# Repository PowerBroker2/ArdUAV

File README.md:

<br />

Code repository for ground station and flight control software for experimental Arduino UAVs (fixed wing).

# First Flight with ArdUAV:

# Current Test Bird:

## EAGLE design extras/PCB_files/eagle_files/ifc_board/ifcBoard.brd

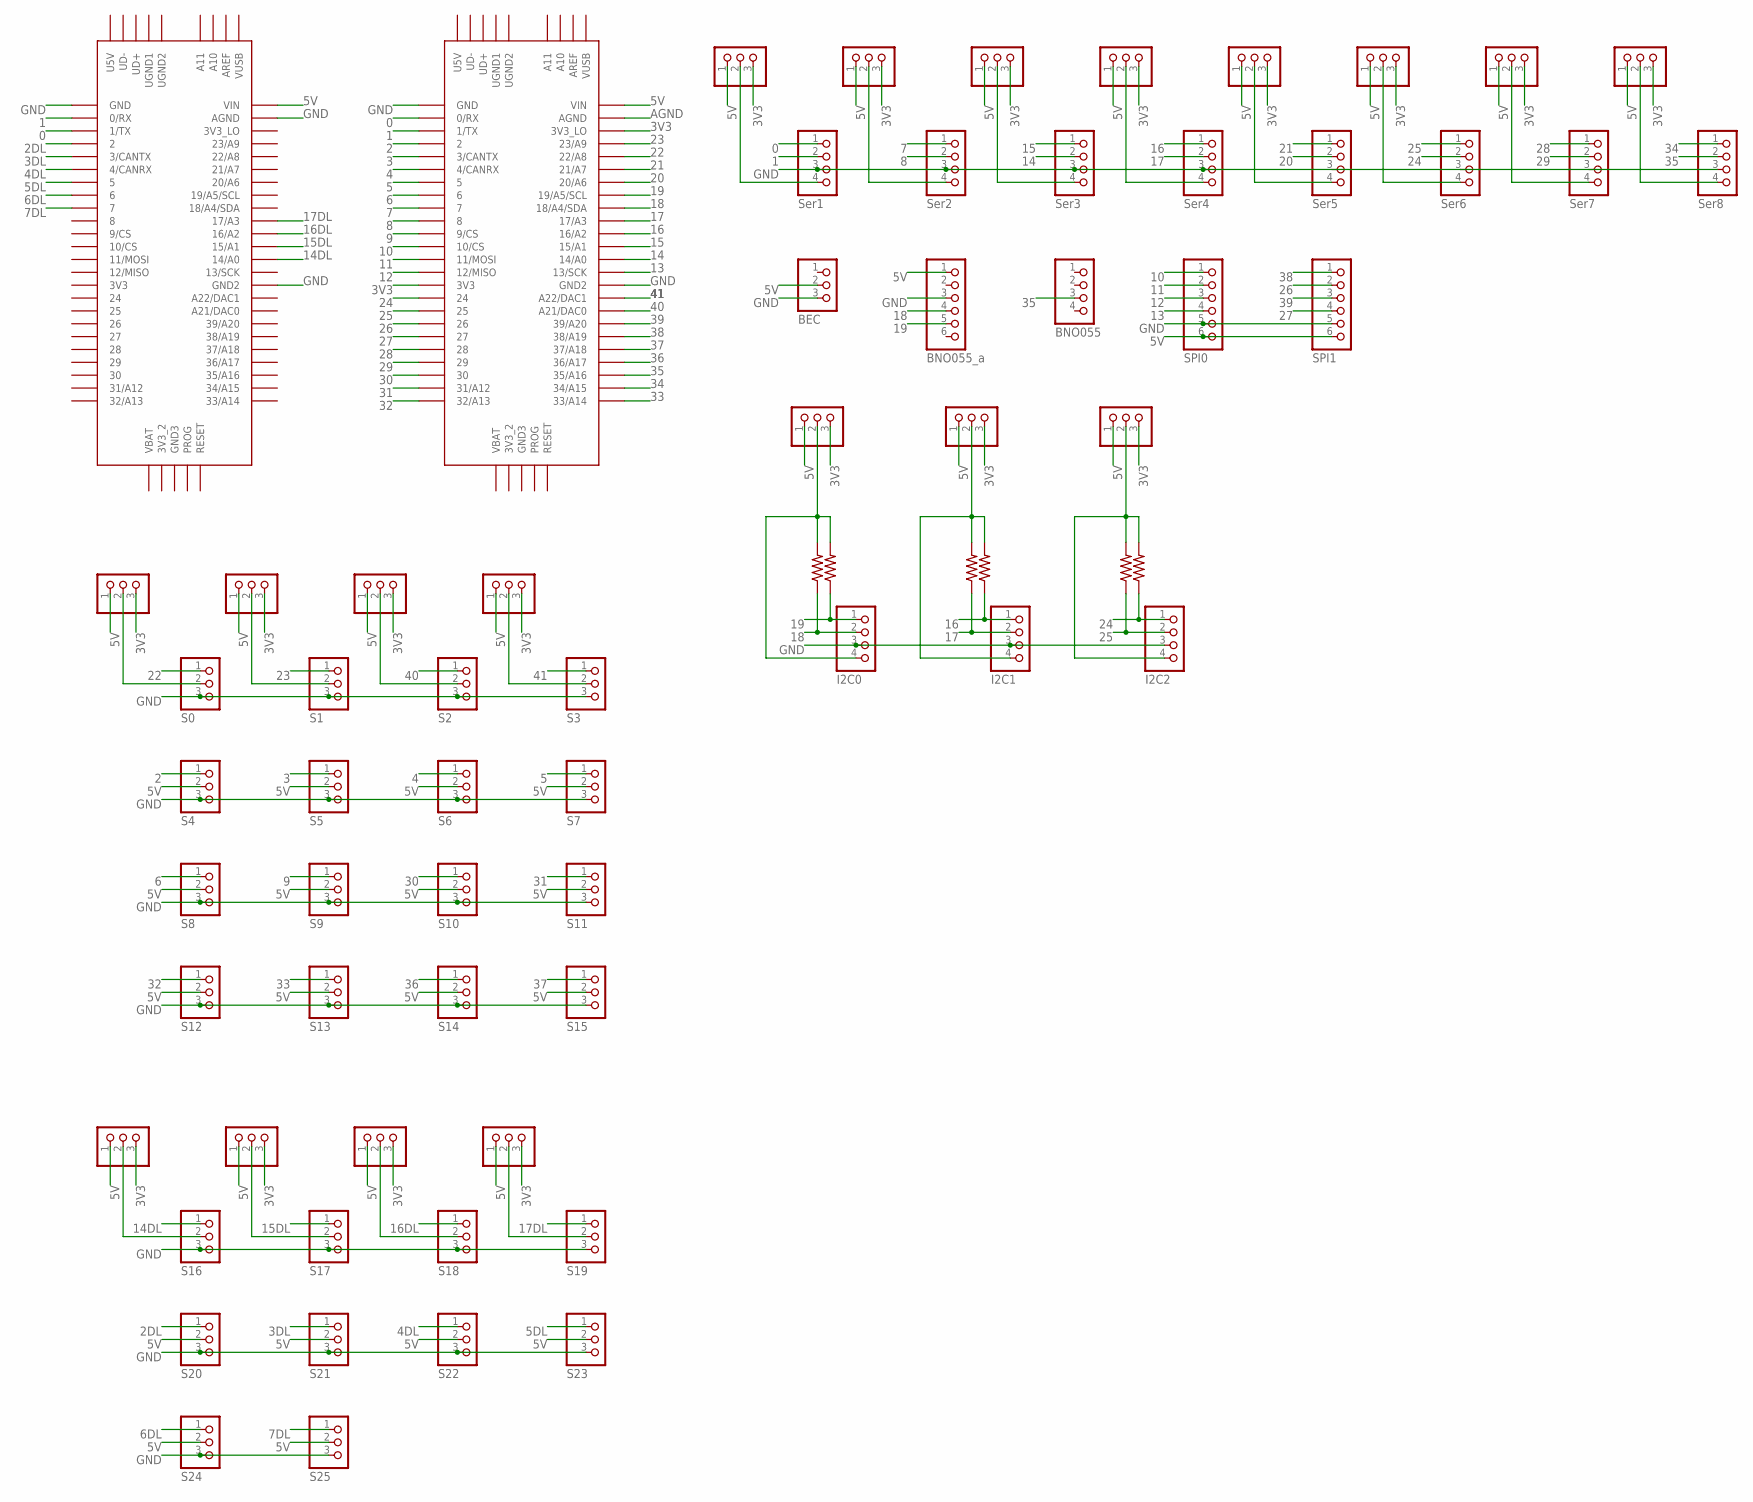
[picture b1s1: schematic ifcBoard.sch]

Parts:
JP1: BEC; 1X03
JP2, JP19, JP20, JP35, JP36, JP37, JP38, JP39, JP40, JP41, JP42, JP43, JP44, JP45, JP46, JP47, JP64, JP65, JP66, JP67: S0; 1X03
JP3: S1; 1X03
JP4: S2; 1X03
JP5: S3; 1X03
JP6: S4; 1X03
JP7: S5; 1X03
JP8: S6; 1X03
JP9: S7; 1X03
JP10: S8; 1X03
JP11: S9; 1X03
JP12: S10; 1X03
JP13: S11; 1X03
JP14: S12; 1X03
JP15: S13; 1X03
JP16: S14; 1X03
JP17: S15; 1X03
JP18: Ser6; 1X04
JP21: Ser7; 1X04
JP22: I2C0; 1X04
JP23: Ser1; 1X04
JP24: Ser2; 1X04
JP25: Ser3; 1X04
JP26: Ser4; 1X04
JP27: Ser5; 1X04
JP28: I2C1; 1X04
JP29: I2C2; 1X04
JP30: Ser8; 1X04
JP31: SPI0; 1X06
JP32: SPI1; 1X06
JP33: BNO055_a; 1X06
JP34: BNO055; 1X04
JP58: S16; 1X03
JP59: S17; 1X03
JP60: S18; 1X03
JP61: S19; 1X03
JP62: S23; 1X03
JP63: S22; 1X03
JP68: S21; 1X03
JP69: S20; 1X03
JP70: S24; 1X03
JP71: S25; 1X03
R2, R3, R4, R5, R6, R7: R-US_0207/12; 0207/12
U$1, U$2: TEENSY_3.5/3.6

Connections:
0: JP23.1, U$1.0/RX, U$2.1/TX
1: JP23.2, U$1.1/TX, U$2.0/RX
2: JP6.1, U$1.2
2DL: JP69.1, U$2.2
3: JP7.1, U$1.3/CANTX
3DL: JP68.1, U$2.3/CANTX
3V3: JP19.3, JP20.3, JP35.3, JP36.3, JP37.3, JP38.3, JP39.3, JP40.3, JP41.3, JP42.3, JP43.3, JP44.3, JP45.3, JP46.3, JP47.3, JP64.3, JP65.3, JP66.3, JP67.3, U$1.3V3, U$1.3V3_LO
4: JP8.1, U$1.4/CANRX
4DL: JP63.1, U$2.4/CANRX
5: JP9.1, U$1.5
5DL: JP62.1, U$2.5
5V: JP1.2, JP6.2, JP7.2, JP8.2, JP9.2, JP10.2, JP11.2, JP12.2, JP13.2, JP14.2, JP15.2, JP16.2, JP17.2, JP19.1, JP20.1, JP22.4, JP31.6, JP32.6, JP33.1, JP35.1, JP36.1, JP37.1, JP38.1, JP39.1, JP40.1, JP40.2, JP41.1, JP42.1, JP43.1, JP44.1, JP45.1, JP46.1, JP47.1, JP62.2, JP63.2, JP64.1, JP65.1, JP66.1, JP67.1, JP68.2, JP69.2, JP70.2, JP71.2, R2.2, R3.2, U$1.VIN, U$2.VIN
6: JP10.1, U$1.6
6DL: JP70.1, U$2.6
7: JP24.1, U$1.7
7DL: JP71.1, U$2.7
8: JP24.2, U$1.8
9: JP11.1, U$1.9/CS
10: JP31.1, U$1.10/CS
11: JP31.2, U$1.11/MOSI
12: JP31.3, U$1.12/MISO
13: JP31.4, U$1.13/SCK
14: JP25.2, U$1.14/A0
14DL: JP58.1, U$2.14/A0
15: JP25.1, U$1.15/A1
15DL: JP59.1, U$2.15/A1
16: JP26.1, JP28.1, R6.1, U$1.16/A2
16DL: JP60.1, U$2.16/A2
17: JP26.2, JP28.2, R4.1, U$1.17/A3
17DL: JP61.1, U$2.17/A3
18: JP22.2, JP33.4, R2.1, U$1.18/A4/SDA
19: JP22.1, JP33.5, R3.1, U$1.19/A5/SCL
20: JP27.2, U$1.20/A6
21: JP27.1, U$1.21/A7
22: JP2.1, U$1.22/A8
23: JP3.1, U$1.23/A9
24: JP18.2, JP29.1, R5.1, U$1.24
25: JP18.1, JP29.2, R7.1, U$1.25
26: JP32.2, U$1.26
27: JP32.4, U$1.27
28: JP21.1, U$1.28
29: JP21.2, U$1.29
30: JP12.1, U$1.30
31: JP13.1, U$1.31/A12
32: JP14.1, U$1.32/A13
33: JP15.1, U$1.33/A14
34: JP30.1, U$1.34/A15
35: JP30.2, JP34.3, U$1.35/A16
36: JP16.1, U$1.36/A17
37: JP17.1, U$1.37/A18
38: JP32.1, U$1.38/A19
39: JP32.3, U$1.39/A20
40: JP4.1, U$1.21/DAC0 (A21/DAC0)
41: JP5.1, U$1.A22/DAC1
AGND: U$1.AGND
GND: JP1.3, JP2.3, JP3.3, JP4.3, JP5.3, JP6.3, JP7.3, JP8.3, JP9.3, JP10.3, JP11.3, JP12.3, JP13.3, JP14.3, JP15.3, JP16.3, JP17.3, JP18.3, JP21.3, JP22.3, JP23.3, JP24.3, JP25.3, JP26.3, JP27.3, JP28.3, JP29.3, JP30.3, JP31.5, JP32.5, JP33.3, JP58.3, JP59.3, JP60.3, JP61.3, JP62.3, JP63.3, JP68.3, JP69.3, JP70.3, JP71.3, U$1.GND, U$1.GND2, U$2.AGND, U$2.GND, U$2.GND2
unnamed: JP19.2, JP23.4
unnamed: JP58.2, JP64.2
unnamed: JP59.2, JP65.2
unnamed: JP60.2, JP66.2
unnamed: JP61.2, JP67.2
unnamed: JP20.2, JP24.4
unnamed: JP25.4, JP35.2
unnamed: JP26.4, JP36.2
unnamed: JP2.2, JP42.2
unnamed: JP27.4, JP37.2
unnamed: JP29.4, JP44.2, R5.2, R7.2
unnamed: JP28.4, JP43.2, R4.2, R6.2
unnamed: JP18.4, JP38.2
unnamed: JP21.4, JP39.2
unnamed: JP30.4, JP41.2
unnamed: JP3.2, JP45.2
unnamed: JP4.2, JP46.2
unnamed: JP5.2, JP47.2

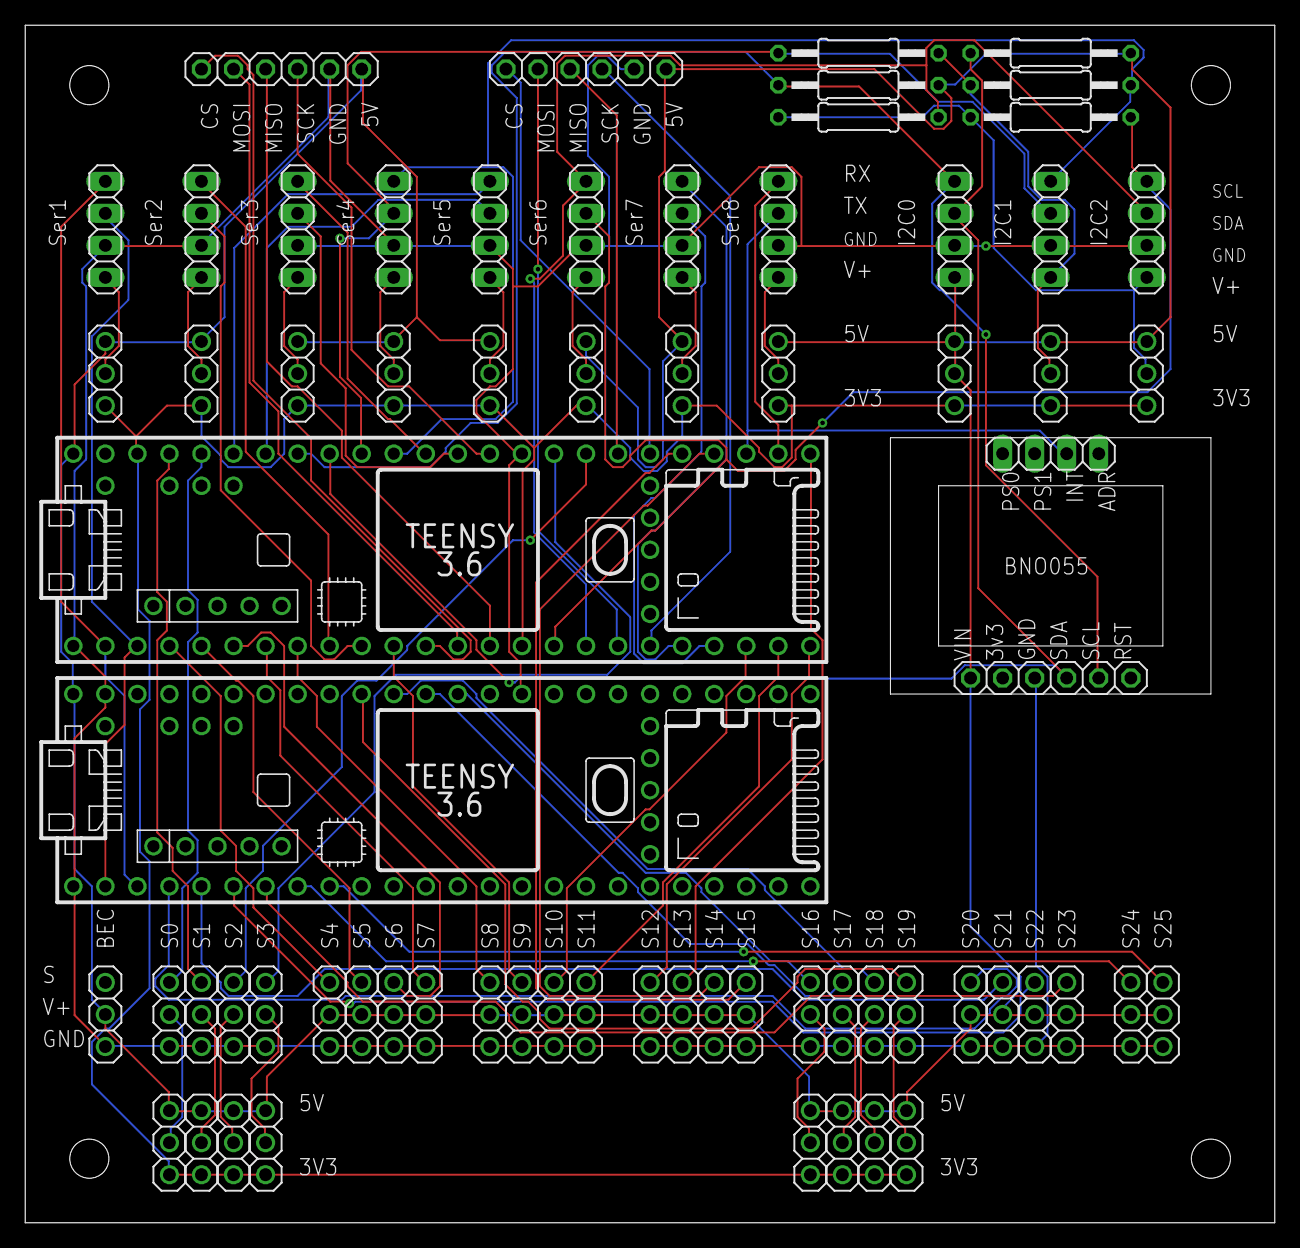
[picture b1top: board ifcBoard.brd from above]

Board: 2 copper layers, 99.0 x 94.9 mm, 69 parts (0 on the bottom side), 73 nets.

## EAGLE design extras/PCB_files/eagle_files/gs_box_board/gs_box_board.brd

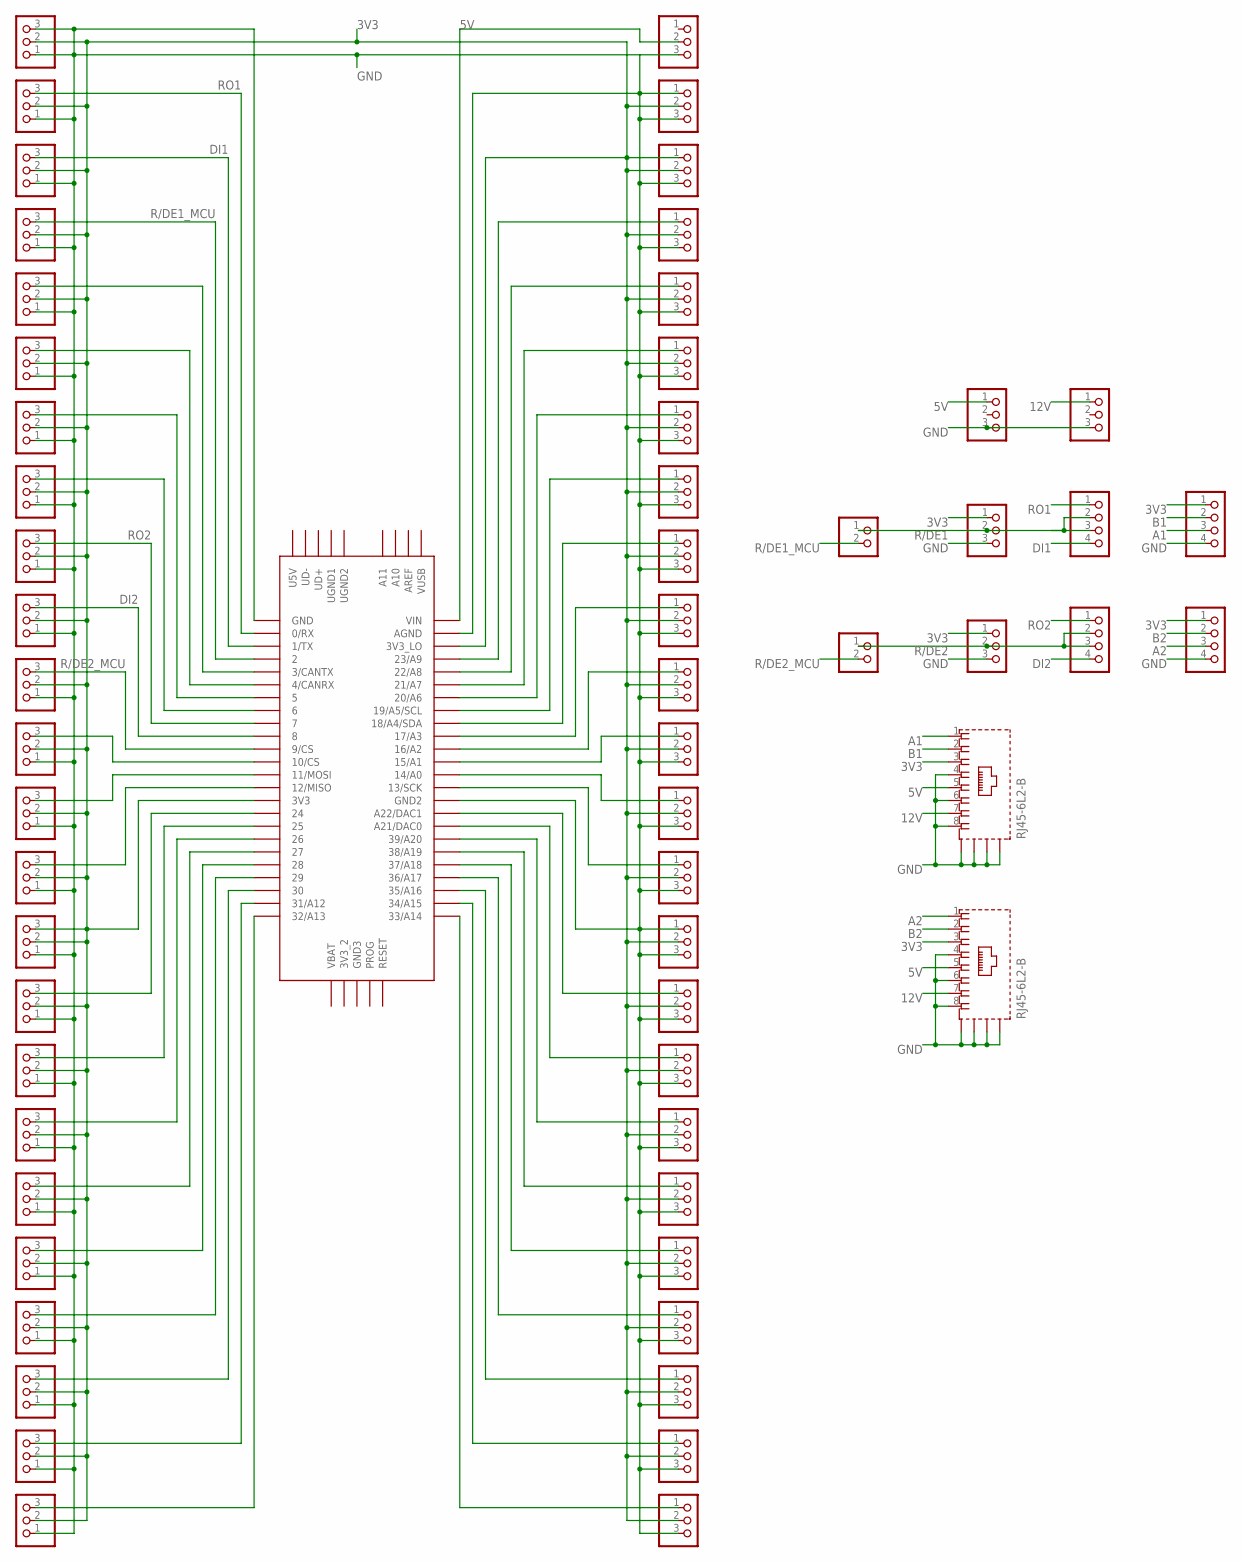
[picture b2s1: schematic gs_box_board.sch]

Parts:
JP1, JP2, JP3, JP4, JP5, JP6, JP7, JP8, JP9, JP10, JP11, JP12, JP13, JP14, JP15, JP16, JP17, JP18, JP19, JP20, JP21, JP22, JP23, JP24, JP25, JP26, JP27, JP28, JP29, JP30, JP31, JP32, JP33, JP34, JP35, JP36, JP37, JP38, JP39, JP40, JP41, JP42, JP43, JP44, JP45, JP46, JP47, JP48, JP53, JP54, JP55, JP56: PINHD-1X3; 1X03
JP49, JP50, JP51, JP52: PINHD-1X4; 1X04
JP57, JP58: PINHD-1X2; 1X02
U$1: TEENSY_3.5/3.6
X1, X2: RJ45-6L2-B; RJ45-SHIELD2

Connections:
3V3: JP1.2, JP2.2, JP3.2, JP4.2, JP5.2, JP6.2, JP6.3, JP7.2, JP8.2, JP9.2, JP10.2, JP11.2, JP12.2, JP13.2, JP14.2, JP15.2, JP16.2, JP17.2, JP18.2, JP19.2, JP20.2, JP22.2, JP23.1, JP23.2, JP24.2, JP25.2, JP26.2, JP27.2, JP28.2, JP29.2, JP30.2, JP31.2, JP32.2, JP33.2, JP34.2, JP35.2, JP36.2, JP37.2, JP38.2, JP39.2, JP40.2, JP41.2, JP42.2, JP43.2, JP44.2, JP45.2, JP46.2, JP47.2, JP48.2, JP50.1, JP52.1, JP53.1, JP54.1, U$1.3V3, U$1.3V3_LO, X1.3, X2.3
5V: JP21.2, JP56.1, U$1.VIN, X1.5, X2.5
12V: JP55.1, X1.7, X2.7
A1: JP50.3, X1.1
A2: JP52.3, X2.1
B1: JP50.2, X1.2
B2: JP52.2, X2.2
DI1: JP34.3, JP49.4, U$1.1/TX
DI2: JP41.3, JP51.4, U$1.8
GND: JP1.3, JP2.1, JP3.1, JP4.1, JP5.1, JP6.1, JP7.1, JP8.1, JP9.1, JP10.1, JP11.1, JP12.3, JP13.3, JP14.3, JP15.1, JP15.3, JP16.3, JP17.3, JP18.3, JP19.3, JP20.3, JP21.3, JP22.1, JP22.3, JP23.3, JP24.3, JP25.3, JP26.3, JP27.3, JP28.3, JP29.3, JP30.3, JP31.3, JP32.1, JP32.3, JP33.1, JP34.1, JP35.1, JP36.1, JP37.1, JP38.1, JP39.1, JP40.1, JP41.1, JP42.1, JP43.1, JP44.1, JP45.1, JP46.3, JP47.3, JP48.3, JP50.4, JP52.4, JP53.3, JP54.3, JP55.3, JP56.3, U$1.AGND, U$1.GND, U$1.GND2, X1.4, X1.6, X1.8, X1.S1 (S), X1.S2 (S), X1.S3 (S), X1.S4 (S), X2.4, X2.6, X2.8, X2.S1 (S), X2.S2 (S), X2.S3 (S), X2.S4 (S)
unnamed: JP36.3, U$1.3/CANTX
unnamed: JP37.3, U$1.4/CANRX
unnamed: JP38.3, U$1.5
unnamed: JP39.3, U$1.6
unnamed: JP3.3, U$1.10/CS
unnamed: JP4.3, U$1.11/MOSI
unnamed: JP5.3, U$1.12/MISO
unnamed: JP7.3, U$1.24
unnamed: JP8.3, U$1.25
unnamed: JP9.3, U$1.26
unnamed: JP10.3, U$1.27
unnamed: JP11.3, U$1.28
unnamed: JP42.3, U$1.29
unnamed: JP43.3, U$1.30
unnamed: JP44.3, U$1.31/A12
unnamed: JP45.3, U$1.32/A13
unnamed: JP24.1, U$1.23/A9
unnamed: JP25.1, U$1.22/A8
unnamed: JP26.1, U$1.21/A7
unnamed: JP27.1, U$1.20/A6
unnamed: JP28.1, U$1.19/A5/SCL
unnamed: JP29.1, U$1.18/A4/SDA
unnamed: JP30.1, U$1.17/A3
unnamed: JP1.1, U$1.16/A2
unnamed: JP12.1, U$1.15/A1
unnamed: JP13.1, U$1.14/A0
unnamed: JP14.1, U$1.13/SCK
unnamed: JP16.1, U$1.A22/DAC1
unnamed: JP17.1, U$1.21/DAC0 (A21/DAC0)
unnamed: JP18.1, U$1.39/A20
unnamed: JP19.1, U$1.38/A19
unnamed: JP20.1, U$1.37/A18
unnamed: JP31.1, U$1.36/A17
unnamed: JP46.1, U$1.35/A16
unnamed: JP47.1, U$1.34/A15
unnamed: JP48.1, U$1.33/A14
R/DE1: JP49.2, JP49.3, JP53.2, JP58.1
R/DE1_MCU: JP35.3, JP58.2, U$1.2
R/DE2: JP51.2, JP51.3, JP54.2, JP57.1
R/DE2_MCU: JP2.3, JP57.2, U$1.9/CS
RO1: JP33.3, JP49.1, U$1.0/RX
RO2: JP40.3, JP51.1, U$1.7

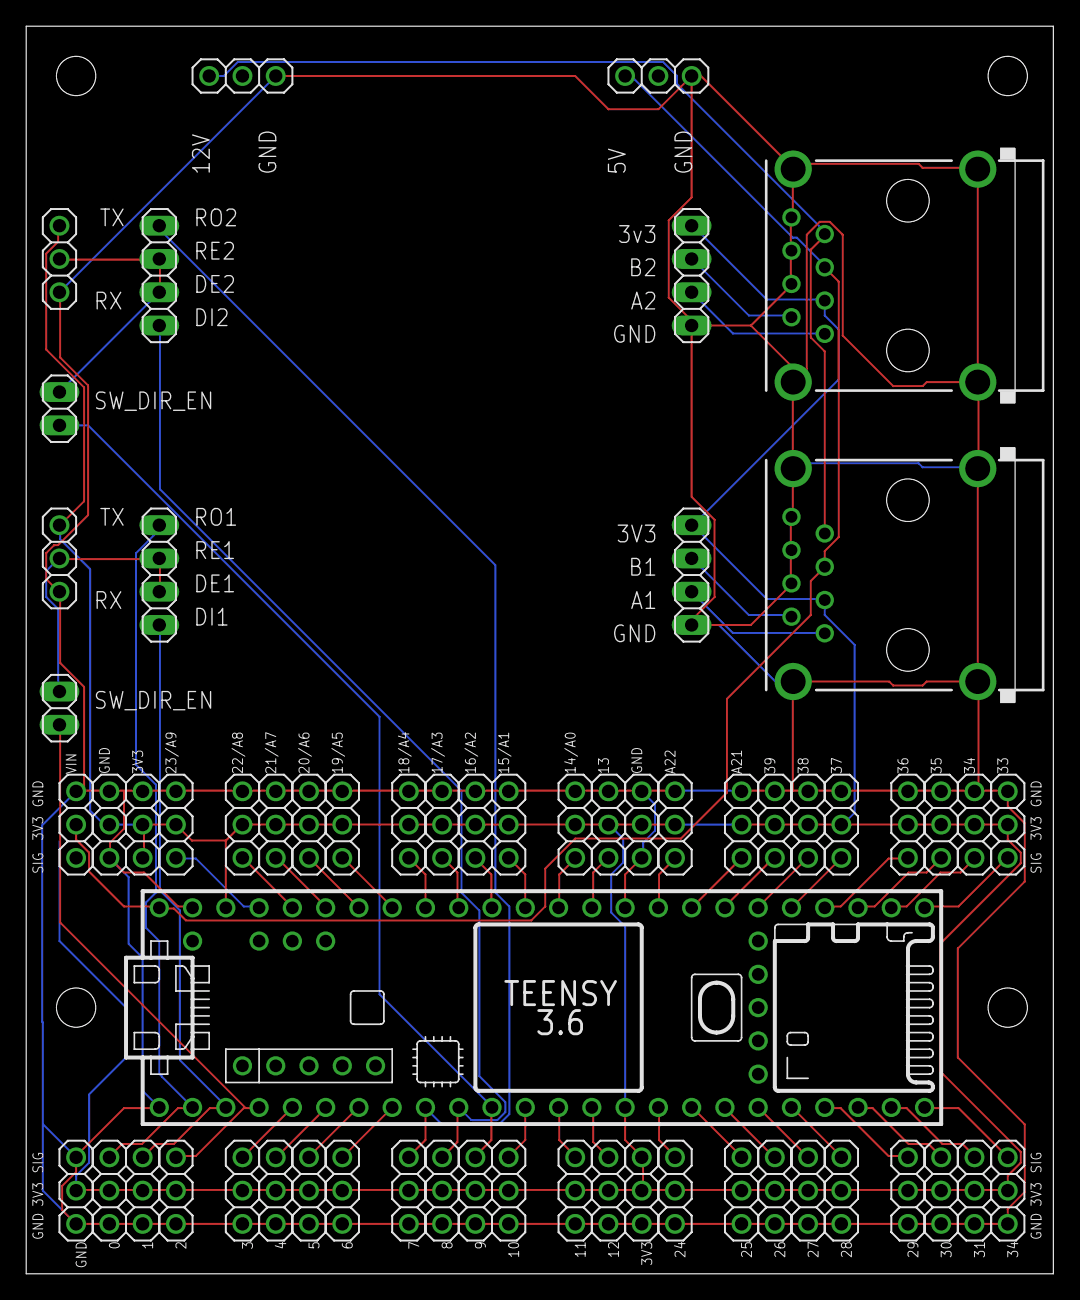
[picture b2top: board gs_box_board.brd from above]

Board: 2 copper layers, 78.4 x 95.2 mm, 61 parts (0 on the bottom side), 52 nets.

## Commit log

2020-01-05 Specify library dependencies in library.properties
    Specifying the library dependencies in the depends field of library.properties causes the Arduino Library Manager (Arduino IDE 1.8.10 and newer) to offer to install any missing dependencies during in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
2020-06-15 Link timeout bug fix
2020-12-19 Update config software and pcb files for new board designs
2020-12-19 Update pictures/video
2020-12-20 Edit visibility of certain base members
2020-12-20 Edit port numbers
2020-12-24 Fix IMU orientation
2020-12-27 Fix GPS setup process
2020-12-27 Use "packed" attribute to save memory/packet space
2020-12-27 Bug fix
2020-12-29 Update servo pins
2020-12-31 Make IMU settings more configurable
2020-12-31 Add new IMU settings
